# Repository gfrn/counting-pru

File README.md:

## CountingPRU - _SIRIUS_
_PRU-based Counters_

Brazilian Synchrotron Light Laboratory (LNLS/CNPEM)
Controls Group

___

_Author:_

Patricia H. Nallin ( _patricia.nallin@lnls.br_ )

_____
_Brief Description:_

Designed as a PRU-based system, this product was developed in order to count trains of pulses during a period of time either from Bergoz Differential BLM or from LNLS Gamma Sensors (4-channel standard TTL signal), up to 14 MHz.

The project consists on:

- Hardware files (Cape board for Beaglebone)
- Library (C or Python)
- EPICS IOC (using 'pcaspy' module)

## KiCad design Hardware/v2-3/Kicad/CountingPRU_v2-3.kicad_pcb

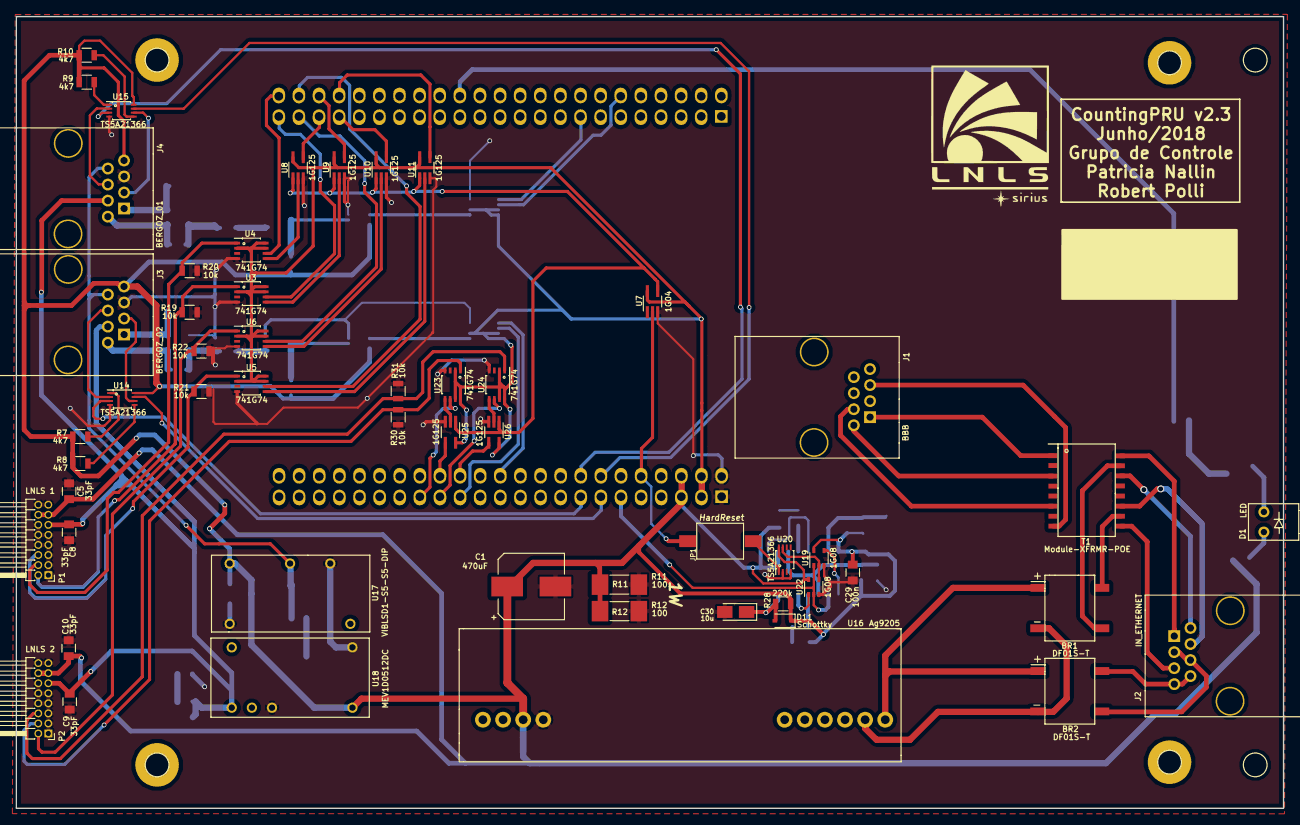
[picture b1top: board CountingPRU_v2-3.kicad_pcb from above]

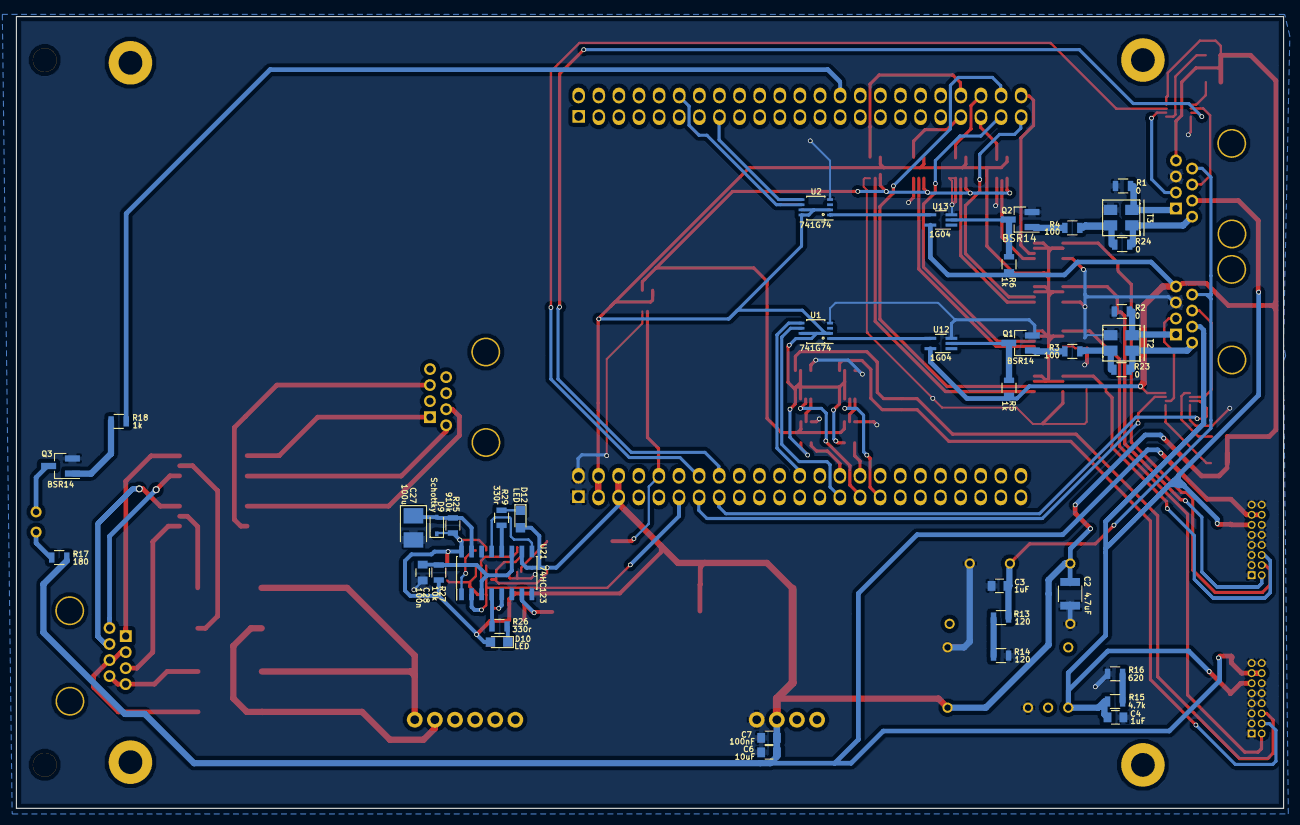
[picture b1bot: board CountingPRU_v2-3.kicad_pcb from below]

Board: 2 copper layers, 160.0 x 100.0 mm, 94 parts (38 on the bottom side), 92 nets.

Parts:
 : C64AC; Eurocard_template
 #2: LNLS_LOGO_Silk
BR1, BR2: DF01S-T; RECT_BRIDGE
Beagle1: BeagleBone; BBB_Upside_Down
C1: 470uF; CP_Elec_8x5.4
C2: 4.7uF; C_1210
C3, C4: 1uF; C_0805
C5, C8, C9, C10: 33pF; C_0805
C6: 10uF; C_0805
C7: 100nF; C_0805
C27: 100u; CP_Tantalum_Case-T_EIA-3528-12_Reflow
C28, C29: 100n; C_0805
C30: 10u; CP_Tantalum_Case-A_EIA-3216-18_Reflow
D1: LED; LED_para_painel_KINGBRIGHT
D9, D11: Schottky; D_SOD-323
D10, D12: LED; LED_0805
J1: BBB; RJ45-STEWART
J2: IN_ETHERNET; RJ45-STEWART
J3: BERGOZ_02; RJ45-STEWART
J4: BERGOZ_01; RJ45-STEWART
JP1: HardReset; DIPSwitchSMD_1pos
P1: LNLS 1; Pin_Header_Angled_2x08_Pitch1.27mm
P2: LNLS 2; Pin_Header_Angled_2x08_Pitch1.27mm
Q1, Q2, Q3: BSR14; SOT-23_Handsoldering
R1, R2, R23, R24: 0; R_0805
R3, R4: 100; R_0805
R5, R6, R18: 1k; R_0805
R7, R8, R9, R10: 4k7; R_0805
R11, R12: 100; R_MELF_MMB-0207
R13, R14: 120; R_0805
R15: 4.7k; R_0805
R16: 620; R_0805
R17: 180; R_0805
R19, R20, R21, R22, R27, R30, R31: 10k; R_0805
R25: 910k; R_0805
R26, R29: 330r; R_0805
R28: 220k; R_0805
T1: Module-XFRMR-POE; module-xfrmr-poe
T2, T3: CMC; Trafo_murata_SMD
U1, U2, U3, U4, U5, U6, U23, U24: 741G74; TSSOP-8
U7, U12, U13: 1G04; SOT-353_SC-70-5_Handsoldering
U8, U9, U10, U11, U25, U26: 1G125; SOT-353_SC-70-5_Handsoldering
U14, U15, U20: TS5A21366; VSSOP-8
U16: Ag9205; 9200-Silvertel
U17: VIBLSD1-S5-S5-DIP; VIBLSD1-DIP
U18: MEV1D0512DC
U19, U22: 1G08; SOT-353_SC-70-5
U21: 74HC123; SOIC-16_3.9x9.9mm_Pitch1.27mm

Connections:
+3.3V: Beagle1.C3, Beagle1.C4, U1.2, U1.7, U1.8, U2.2, U2.7, U2.8, U3.2, U3.7, U3.8, U4.2, U4.7, U4.8, U5.2, U5.7, U5.8, U6.2, U6.7, U6.8, U7.5, U8.5, U9.5, U10.5, U11.5, U23.2, U23.7, U23.8, U24.2, U24.7, U24.8, U25.5, U26.5
+5V: Beagle1.C5, Beagle1.C6, C1.1, C2.1, C5.1, C6.1, C7.1, C10.1, C29.1, D9.1, D10.2, D11.1, D12.2, J3.7, J4.7, P1.13, P1.14, P2.13, P2.14, R5.1, R6.1, R7.1, R8.1, R9.1, R10.1, R11.1, R12.1, R17.1, R25.1, R27.1, R28.1, U12.5, U13.5, U14.8, U15.8, U16.8, U17.14, U18.14, U19.5, U20.8, U21.10, U21.16, U22.5
+24V: C4.1, C8.1, C9.1, J3.3, J4.3, P1.11, P2.11, R15.1, U18.8
-5V: C3.1, J3.8, J4.8, R13.1, U17.11
/Alimentação/RDCT: BR1.2, T1.10
/Alimentação/TDCT: BR1.4, T1.15
/Alimentação/VIN+: BR1.1, BR2.1, U16.1
/Alimentação/VIN-: BR1.3, BR2.3, U16.2
/BR2A: BR2.4, J2.4, J2.5
/BR2B: BR2.2, J2.7, J2.8
/Bergoz/AIN_01: J4.4, U15.2
/Bergoz/AIN_02: J3.4, U14.2
/Bergoz/BIN_01: J4.5, U15.6
/Bergoz/BIN_02: J3.5, U14.6
/Bergoz/D+_01: J4.2, R24.2, T3.1
/Bergoz/D+_02: J3.2, R23.2, T2.1
/Bergoz/D-_01: J4.1, R1.2, T3.2
/Bergoz/D-_02: J3.1, R2.2, T2.2
/Bergoz/SINAL_1: U2.1, U13.4
/Bergoz/SINAL_2: U1.1, U12.4
/CH1: Beagle1.C13, U14.7
/CH2: Beagle1.C15, U14.3
/CH3: Beagle1.C14, U15.7
/CH4: Beagle1.C16, U15.3
/CLEAR_1: Beagle1.B12, U2.6
/CLEAR_2: Beagle1.C27, U1.6
/CLEAR_3: Beagle1.B45, U3.6
/CLEAR_4: Beagle1.B46, U4.6
/CLEAR_5: Beagle1.B44, U5.6
/CLEAR_6: Beagle1.B43, U6.6
/CLEAR_7: Beagle1.C31, U23.6
/CLEAR_8: Beagle1.C29, U24.6
/CONTA_1: Beagle1.B15, U2.5
/CONTA_2: Beagle1.C24, U1.5
/CONTA_3: U3.5, U9.2
/CONTA_3_BBB: Beagle1.B42, U9.4
/CONTA_4: U4.5, U8.2
/CONTA_4_BBB: Beagle1.B41, U8.4
/CONTA_5: U5.5, U11.2
/CONTA_5_BBB: Beagle1.B40, U11.4
/CONTA_6: U6.5, U10.2
/CONTA_6_BBB: Beagle1.B39, U10.4
/CONTA_7: U23.5, U25.2
/CONTA_7_BBB: Beagle1.C30, U25.4
/CONTA_8: U24.5, U26.2
/CONTA_8_BBB: Beagle1.C28, U26.4
/GPIO_RST: Beagle1.C11, U19.1, U21.2, U22.2
/HardReset_BBB/HARD_RST: JP1.1, U20.1
/HardReset_BBB/RST_RST: C28.1, R27.2, U21.3, U21.11
/HardReset_BBB/pontoRST: U19.2, U20.7, U22.4
/HardReset_BBB/pulsRST: U21.5, U22.1
/HardReset_BBB/pulsoWAIT: U21.9, U21.13
/LED: Beagle1.B28, R18.2
/RD1: J2.3, T1.11
/RD2: J2.6, T1.9
/RX+: J1.3, T1.6
/RX-: J1.6, T1.8
/SINAL_3: P1.2, R19.1, U3.1
/SINAL_4: P1.4, R20.1, U4.1
/SINAL_5: P1.6, R21.1, U5.1
/SINAL_6: P2.2, R22.1, U6.1
/SINAL_7: P2.4, R30.1, U23.1
/SINAL_8: P2.6, R31.1, U24.1
/SYS_RST: Beagle1.C10, JP1.2, U7.2
/TD1: J2.1, T1.16
/TD2: J2.2, T1.14
/TX+: J1.1, T1.1
/TX-: J1.2, T1.3
/~SYS_RST: U7.4, U8.1, U9.1, U10.1, U11.1, U25.1, U26.1
GND: Beagle1.C1, Beagle1.C2, C1.2, C2.2, C3.2, C4.2, C5.2, C6.2, C7.2, C8.2, C9.2, C10.2, C27.2, C28.2, C29.2, C30.2, J3.6, J4.6, P1.1, P1.3, P1.5, P1.7, P1.8, P1.9, P1.10, P1.12, P1.15, P1.16, P2.1, P2.3, P2.5, P2.7, P2.8, P2.9, P2.10, P2.12, P2.15, P2.16, Q1.2, Q2.2, Q3.2, R1.1, R2.1, R11.2, R12.2, R14.2, R16.2, R19.2, R20.2, R21.2, R22.2, R30.2, R31.2, T2.3, T3.3, U1.4, U2.4, U3.4, U4.4, U5.4, U6.4, U7.3, U8.3, U9.3, U10.3, U11.3, U12.3, U13.3, U14.4, U15.4, U16.7, U17.1, U17.9, U18.1, U18.10, U19.3, U20.2, U20.4, U21.6, U21.8, U21.14, U22.3, U23.4, U24.4, U25.3, U26.3
unnamed: C27.1, D9.2, R25.2, U21.15
unnamed: C30.1, D11.2, R28.2, U21.7
unnamed: D1.1, Q3.3
unnamed: D1.2, R17.2
unnamed: D10.1, R26.1
unnamed: D12.1, R29.1
unnamed: Q1.1, R3.2
unnamed: Q1.3, R5.2, U12.2
unnamed: Q2.1, R4.2
unnamed: Q2.3, R6.2, U13.2
unnamed: Q3.1, R18.1
unnamed: R7.2, U14.1
unnamed: R8.2, U14.5
unnamed: R9.2, U15.1
unnamed: R10.2, U15.5
unnamed: R13.2, R14.1
unnamed: R15.2, R16.1
unnamed: R3.1, R23.1, T2.4
unnamed: R4.1, R24.1, T3.4
unnamed: R26.2, U21.4
unnamed: R29.2, U21.12
unnamed: U19.4, U21.1

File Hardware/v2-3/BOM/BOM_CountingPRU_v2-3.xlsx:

Designator | Description | Value | PartNumber | Package | Manufacturer | Quantity | CNPEM Part Number | OBS | Packaging
Beagle1 | 2x Pin Heander para a BeagleBone Black | BeagleBone | ZW-23-12-F-D-754-178 | 2x Straight_2x23 pitch 2.54mm | SAMTEC | 2 | MT104047 |  | Unit
BR1,BR2 | Bridge Rectifier Single Phase Standard 100V SMD | Diode_Bridge | DF01S-T | RECT_BRIDGE | Diodes Incorporated | 2 | MT107907 |  | Tape
C1 | Aluminum Electrolytic Capacitors Radial SMD 470µF 16V | 470uF | EEE-1CA471UP | CP_Elec_8x5.4 | Panasonic Electronic Components | 1 | AP106777 |  | Tape
C2 | Multilayer Ceramic Capacitors 4.7µF 50V ±10% X7R 1210 SMD | 4.7uF | GRM21BR61E475MA12L | 1210 | Murata | 1 | MT104428 |  | Reel
C27 | Tantalum Capacitor 100uF, 10V, 20%, ESR 0.9ohm | 100uF | TLJT107M010R0900 | 1210 | AVX | 1 | MT103959 |  | Tape
C3,C4 | Ceramic Capacitor SMD ±5% 16V X7R | 1uF | C0805C105J4RACTU | 0805 | AVX | 2 | MT109488 |  | Reel
C30 | Tantalum Capacitor 10uF, 10V, 10%, ESR 3.8ohm | 10uF | 08053C105JAT2A | 1206 | Kemet | 1 | AP111595 |  | Tape
C6 | Ceramic Capacitor 10uF 16V 10% SMD 0805 X5R | 10uF | CL21A106KOQNNNE | 0805 | Samsung ElectroMechanics | 1 | MT104058 |  | Reel
C7,C28,C29 | Multilayer Ceramic Capacitor 100nF 50V 5% SMD 0805 X7R | 100nF | GCM21BR72A104KA37L | 0805 | Murata | 3 | MT114854 |  | Reel
C8,C5,C9,C10 | Ceramic Capacitor 33pF 50V 10% SMD 0805 C0G/NP0 | 33pF | 08055A330JAT2A | 0805 | AVX | 4 | MT112460 |  | Reel
D1 | LED Circuit Board Indicator Single Red Diffused, Through Hole, Right Angle 2V 2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 | LED-Red | WP934CB/ID | 2x1 PTH pitch 2,54mm | Kingbright | 1 | AP110389 |  | Unit
D9,D11 | Diode Schottky 40V 750mA (DC) Surface Mount | Schottky | BAT165E6327HTSA1 | SOD-323 | Infineon Technologies | 2 | MT104048 |  | Tape
D10,D12 | Red LED, 2V, 20mA, SMD 0805 | LED Red | LTST-C171KRKT | 0805 | Lite-On Inc | 2 | AP111653 |  | Reel
J1,J2,J3,J4 | RJ45 Jack Connector Right Angle | RJ45 | SS-60000-010 | RJ45-STEWART | Stewart | 4 | MT107916 |  | Tube
JP1 | DIP Switch SMD 1 position | Dip Switch 1 pos | KAE01SGGT | DIP Switch SMD 1 position | E-Switch | 1 | MT104049 |  | Tube
P1,P2 | Connector 90° PTH 02x08 | CONN_02X08 | 3221-16-0200-00 | 2x08_PTH_Pitch1.27mm | CNC Tech | 2 | MT107378 |  | Unit
Q3,Q2,Q1 | Bipolar (BJT) Transistor NPN SMD 40V 800mA 300MHz 350mW | BSR14 | BSR14 | SOT-23 | Fairchild Semiconductor | 3 | MT104051 |  | Tape
R11,R12 | Resistor SMD 100Ω ±1% 1W Thin Film | 100 | MMB02070C1000FB200 | MELF 0207 | Vishay | 2 | MT112459 |  | Reel
R13,R14 | Resistor SMD 120 Ω ±1% 0.125W Thick Film | 120 | 0805W8F1200T5E | 0805 | RoyalOhm | 2 | MT115760 |  | Reel
R16 | Resistor SMD 620Ω ±1% 0.125W Thick Film | 620 | RK73H2ATTD6200F | 0805 | KOA Speer | 1 | MT109494 |  | Reel
R17 | Resistor SMD 180 ohm 1% 1/8W Thin Film | 180 | 0805W8F1800T5E | 0805 | RoyalOhm | 1 | MT114496 |  | Reel
R18,R5,R6 | Resistor SMD 1K ohm 1% 1/8W Thick Film | 1k | 0805W8F1001T5E | 0805 | RoyalOhm | 3 | MT109492 |  | Reel
R19,R20,R21,R22,R27,R30,R31 | Resistor SMD 10 kΩ ±1% 0.125W Thick Film | 10k | 0805W8F1002T5E | 0805 | RoyalOhm | 7 | MT109485 |  | Reel
R23,R2,R1,R24 | Resistor SMD 0 Ohms 0.125W Thick Film | 0 | RC0805JR-070RL | 0805 | Yageo | 4 | MT100803 | NÃO DEVEM SER MONTADOS | NÃO SERÁ FORNECIDO
R25 | Resistor 910K ohm 1% 1/8W SMD 0805 Thick Film | 910KΩ | 0805W8F9103T5E | 0805 | RoyalOhm | 1 | MT115761 |  | Reel
R26,R29 | Resistor 330 ohm, 1/8W, SMD 0805, Thick Film | 330Ω | 0805W8F3300T5E | 0805 | RoyalOhm | 2 | MT115762 |  | Reel
R28 | Resistor 220K ohm 1% 1/8W SMD 0805 Thick Film | 220kΩ | 0805W8F2203T5E | 0805 | RoyalOhm | 1 | MT115763 |  | Reel
R3,R4 | Resistor SMD 100Ω ±1% 0.125W Thick Film | 100 | RK73H2ATTD1000F | 0805 | KOA Speer | 2 | MT115765 |  | Reel
R7,R8,R9,R10, R15 | Resistor SMD 4.7 kΩ ±1% 0.125W Thick Film | 4k7 | 0805W8F4701T5E | 0805 | RoyalOhm | 4 | MT115764 |  | Reel
T1 | Module XFRMR LAN 10/100 PoE SMD | Module-XFRMR-POE | S558-5500-25-F | Module-XFRMR-Poe | Bel Fuse Inc. | 1 | MT107908 |  | Tape
T2,T3 | 2 Line Common Mode Choke Surface Mount 500 Ohm @ 100MHz 4A DCR 27 mOhm | Transformer_1P_1S | DLW5BTM501SQ2L | Horizontal, 6 PC Pad | Murata | 2 | MT109675 |  | Tape
U1,U2,U3,U4,U5,U6,U23,U24 | Single D-type Flip-flop | 741G74 | 296-25554-2-ND | TSSOP-8 | Texas Instruments | 8 | AP105702 |  | Tape
U14,U15,U20 | 2 Circuit IC Switch 1:1 1Ω US8 | TS5A21366 | TS5A21366DCUR | VSSOP-8 | Texas Instruments | 3 | AP109801 |  | Tape
U16 | Isolated PoE module Output 5V – 13W | Ag9200 | AG9205S | 9200-Silvertel | Silvertel | 1 | MT107905 |  | Unit
U17 | Isolated Module DC DC Converter 5V→5V 200mA 1W | VIBLSD1-S5-S5-DIP | VIBLSD1-S5-S5-DIP | 14-DIP-5 Leads | CUI Inc. | 1 | MT108027 |  | Tube
U18 | Isolated Module DC DC Converter 5V→±12V 42mA 1W | MEV1D0512DC | MEV1D0512DC | 14-DIP-6 Leads | Murata Power Solutions Inc. | 1 | MT108008 |  | Tube
U19,U22 | IC Single 2-input AND Gate SMD SOT-353 | 1G08 | 74AHC1G08SE-7 | SOT-353 | Diodes Inc | 2 | MT104245 |  | Reel
U21 | IC 74HC123 SMD SOIC-16 | 74HC123 | 74HC123D | SOIC-16 | NXP Semiconductors | 1 | AP111593 |  | Tape
U7,U12,U13 | Buffer Inverting 1 channel SMD | 1G04 | 74AHC1G04SE-7 | SOT-353 | Diodes Inc | 3 | MT104246 |  | Reel
U8,U9,U10,U11,U25,U26 | Buffer Non-Inverting Push-Pull Output | 1G125 | 74AHC1G125SE-7 | SOT-353 | Nexperia Inc | 6 | MT103958 |  | Reel

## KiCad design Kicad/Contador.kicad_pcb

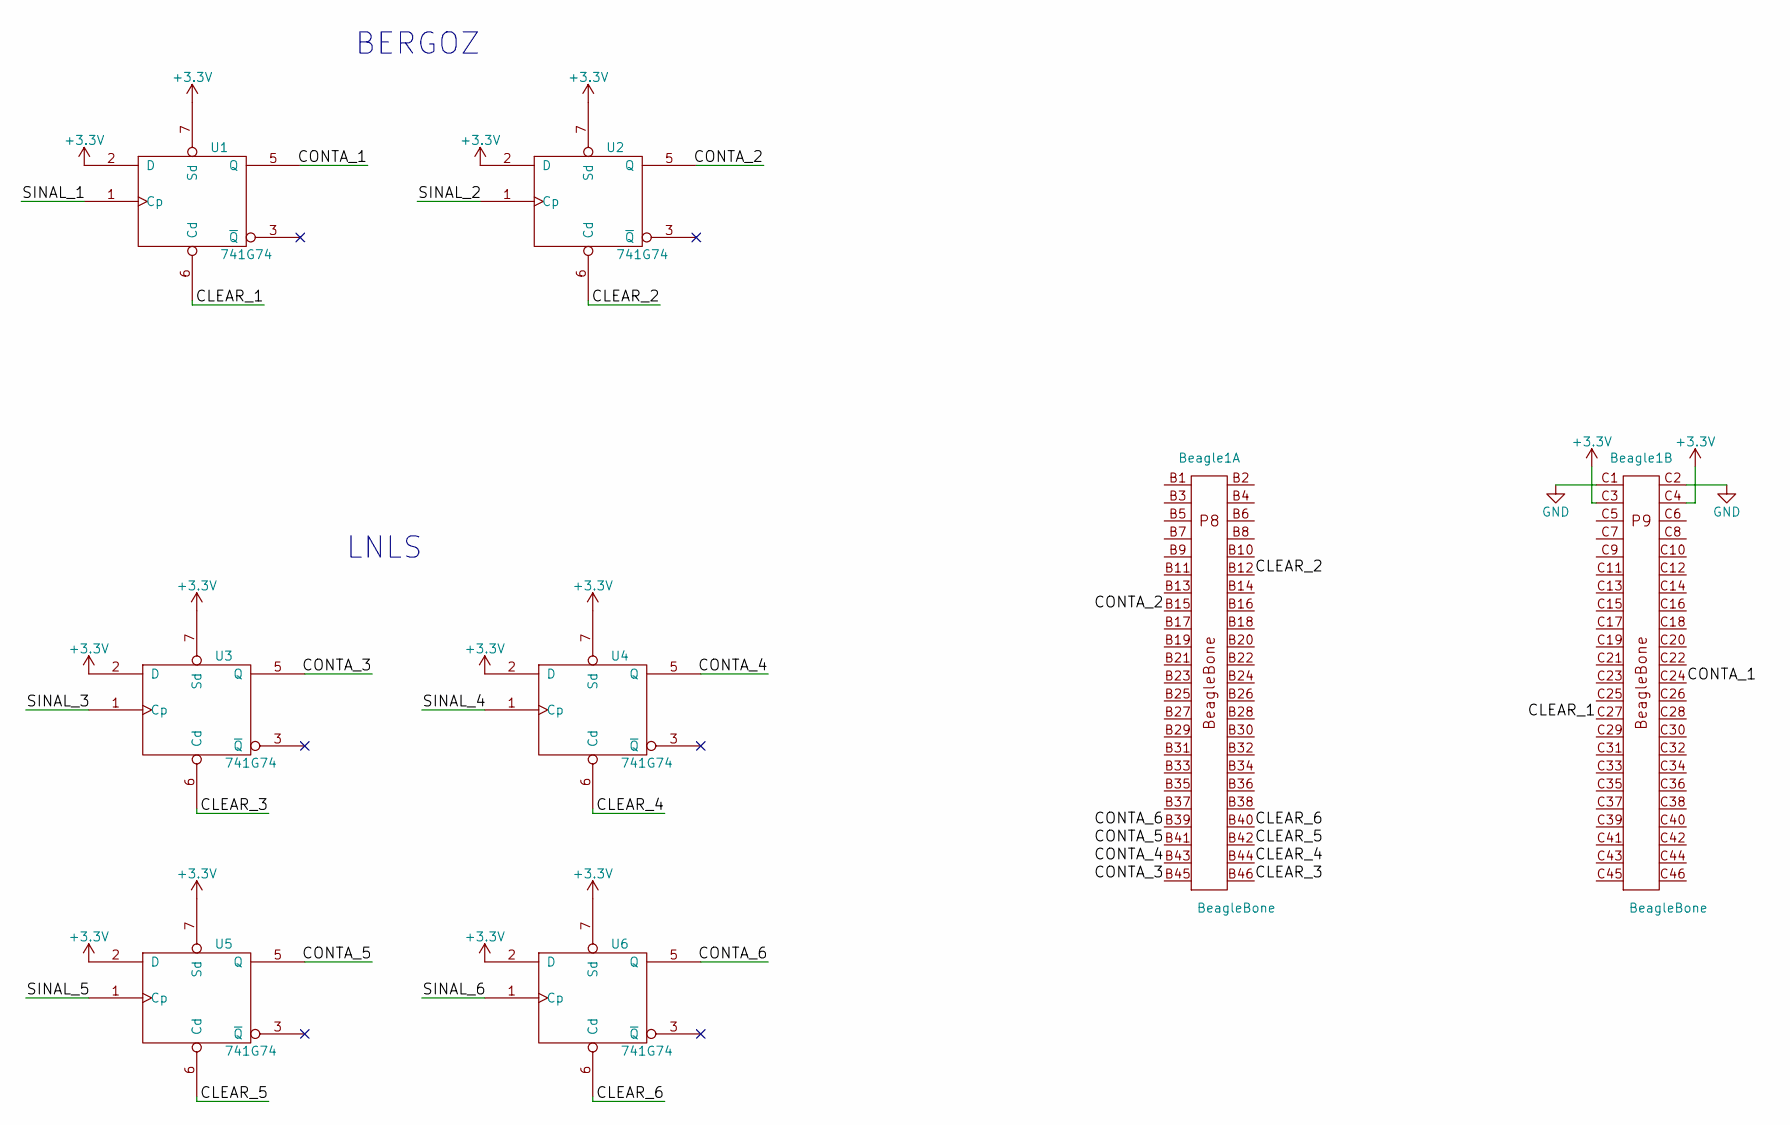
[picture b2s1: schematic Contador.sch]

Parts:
Beagle1: BeagleBone; BEAGLEBONEBLACK
U1, U2, U3, U4, U5, U6: 741G74; TSSOP-8

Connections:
+3V3: Beagle1.C3, Beagle1.C4, U1.2 (D), U1.7 (Sd), U1.8 (VCC), U2.2 (D), U2.7 (Sd), U2.8 (VCC), U3.2 (D), U3.7 (Sd), U3.8 (VCC), U4.2 (D), U4.7 (Sd), U4.8 (VCC), U5.2 (D), U5.7 (Sd), U5.8 (VCC), U6.2 (D), U6.7 (Sd), U6.8 (VCC)
/CLEAR_1: Beagle1.C27, U1.6 (Cd)
/CLEAR_2: Beagle1.B12, U2.6 (Cd)
/CLEAR_3: Beagle1.B46, U3.6 (Cd)
/CLEAR_4: Beagle1.B44, U4.6 (Cd)
/CLEAR_5: Beagle1.B42, U5.6 (Cd)
/CLEAR_6: Beagle1.B40, U6.6 (Cd)
/CONTA_1: Beagle1.C24, U1.5 (Q)
/CONTA_2: Beagle1.B15, U2.5 (Q)
/CONTA_3: Beagle1.B45 (C45), U3.5 (Q)
/CONTA_4: Beagle1.B43, U4.5 (Q)
/CONTA_5: Beagle1.B41, U5.5 (Q)
/CONTA_6: Beagle1.B39, U6.5 (Q)
/SINAL_1: U1.1 (Cp)
/SINAL_2: U2.1 (Cp)
/SINAL_3: U3.1 (Cp)
/SINAL_4: U4.1 (Cp)
/SINAL_5: U5.1 (Cp)
/SINAL_6: U6.1 (Cp)
GND: Beagle1.C1, Beagle1.C2, Beagle1.C45, Beagle1.C46, U1.4 (GND), U2.4 (GND), U3.4 (GND), U4.4 (GND), U5.4 (GND), U6.4 (GND)

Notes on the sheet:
LNLS
BERGOZ

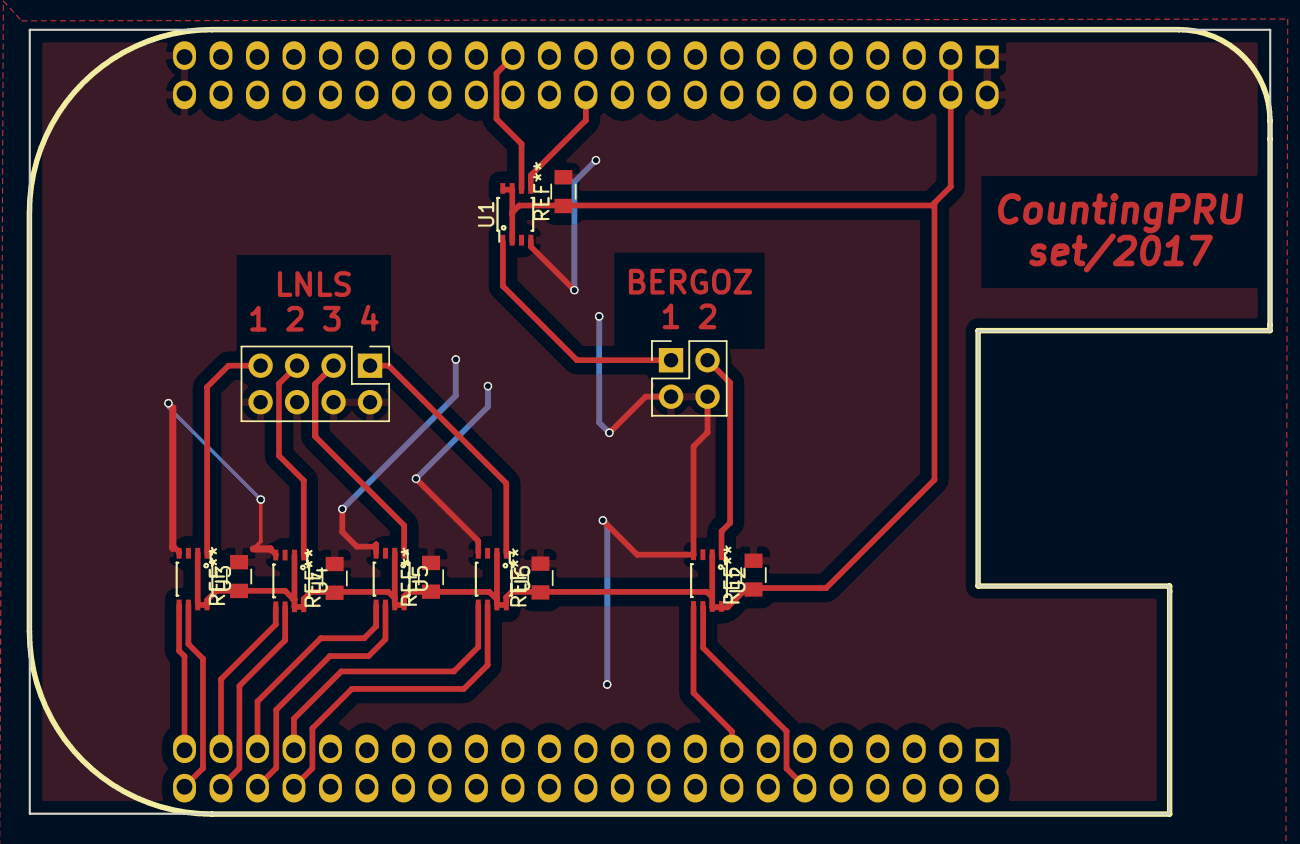
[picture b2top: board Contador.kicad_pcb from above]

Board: 2 copper layers, 86.3 x 54.6 mm, 7 parts (0 on the bottom side), 14 nets.

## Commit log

2017-02-24 modified: .gitignore deleted: .gitignore~ deleted: Reflexao.pyc
2017-02-24 modified: .gitignore
2017-03-17 Minor updates
2017-03-27 Update - New IOC for SV
2017-03-27 deleted: src/.gitignore deleted: src/Reflexao.py deleted: src/build.sh deleted: src/libraries/Reflexao-00A0.dts deleted: src/libraries/Reflexao.c deleted: src/libraries/Reflexao.h deleted: src/librar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
2017-03-28 New OPI for SV
2017-09-15 Revert "New OPI for SV"
    This reverts commit 7fca5fc2a691c17201e85b0f085bbbf81dd4302e.
2018-01-18 Updated files and library. New SI version
2018-02-16 New SI and Hardware files - BaseTime via EPICS
2018-02-21 new SI, considering Bergoz calibration
2018-03-26 Updating files for 2 LNLS connector
2018-03-27 IOC files added and hardware v2-2 updated
2018-03-27 Minor changes
2018-04-04 Adding comments to src codes
2018-04-04 README
2018-04-05 Readme for library
2018-04-05 Documentation
2018-04-05 Update gitignore
2018-04-12 BOM completed
2018-04-17 Update hardware files
2018-05-17 Config pins for kernel 4.14 added
2018-05-21 rc.local file added
2018-07-19 Updating v2-3 hardware files
2018-08-14 Production files added
2018-08-17 Jiga files added
2018-08-20 zip files
2018-08-20 Jiga files updated
2018-09-04 organizing files
2018-09-06 Socket - BSMP protocol - version available
2018-09-06 send 1-byte variable added
2018-09-20 Updating library for python-sirius(3.6) and v2-3 hardware
2018-10-03 Removing useless directories after install
2019-05-07 Redis support for TimeBase and Count values
2019-10-02 Initial timebase
2019-12-10 Counting = pulses per second
2020-02-18 Timebase stored in Redis db
2020-03-16 Storing attached device serial numbers in current board
2020-03-17 Preventing timebase == 0 and correcting minor BSMP changes
2021-04-15 First step in moving some files to Python 3
2021-04-20 Removes unused imports, encodes sent data
2021-04-20 Doesn't ord(), iterate through byte array when extending
2021-04-28 Fixes checksum by removing encoding
2021-04-28 Moves files to their roots, completes Python3 port, adds all unit tests
2021-04-28 Removes Redis from unit tests
2021-04-29 Renames test file, makes other Python files executable
2021-05-07 Removes redundant initializations
2021-09-15 Adds TI kernel/rpmsg version
2021-09-15 Adds second PRU
2021-09-15 Adds firmware compilation instructions
2021-09-17 Starts PRU automatically with script
2021-09-17 Removes debugging info
2021-09-17 Adds build folder to gitignore
2021-09-20 Fixes kick bit on PRU1, improves exceptions for Py lib
2021-09-22 Adds return jump (just to make sure
2021-09-27 Adds setup script, adds commands to config-pin
2021-09-27 Fixes formatting
2021-09-30 Fixes import
2021-10-01 Adds compatible socket script, removes redundant declarations
2021-10-01 Removes unnecessary defines
2021-10-01 Adds import
2021-10-01 Fixes QBBC syntax
2021-11-17 Updates to PSSP 6.0.0
2021-11-25 Creates Makefiles for local building, updates module name
2021-11-25 Build fixes
